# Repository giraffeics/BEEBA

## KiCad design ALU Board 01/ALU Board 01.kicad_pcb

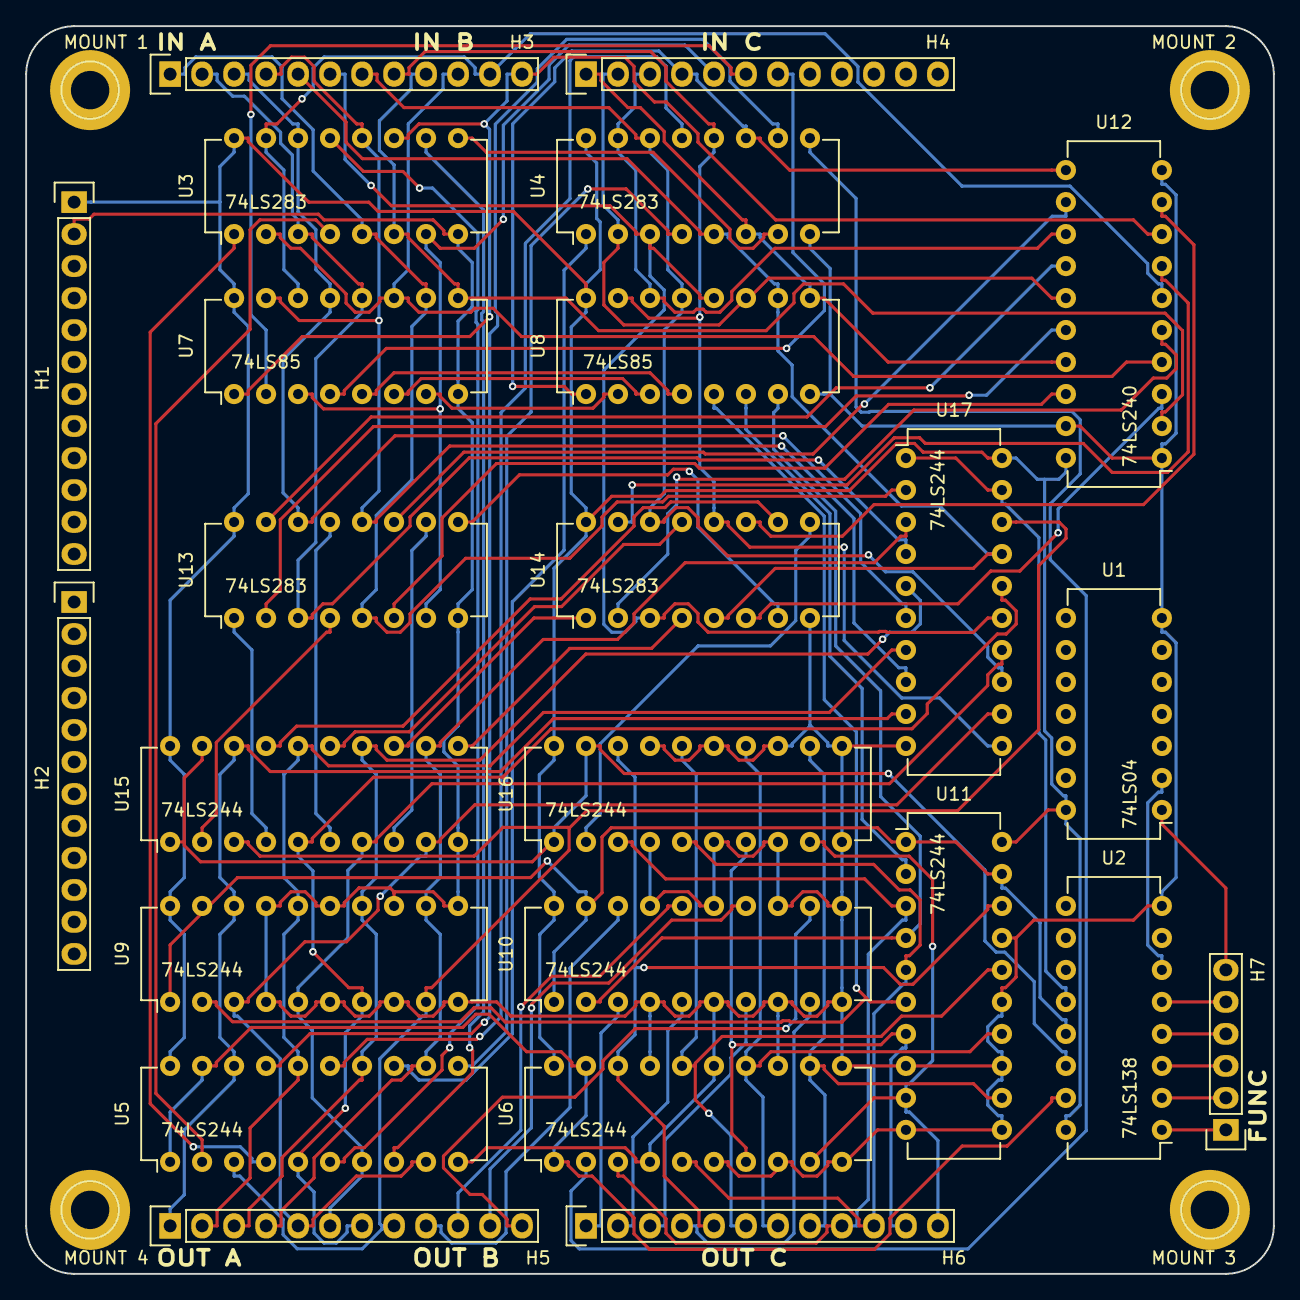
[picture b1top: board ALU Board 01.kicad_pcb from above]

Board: 2 copper layers, 99.1 x 99.1 mm, 28 parts (0 on the bottom side), 90 nets.

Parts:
H1, H2, H3, H4, H5, H6: CONN_01X12; Socket_Strip_Straight_1x12
H7: CONN_01X06; Socket_Strip_Straight_1x06
MOUNT 1, MOUNT 2, MOUNT 3, MOUNT 4: 1pin
U1: 74LS04; DIP-14_W7.62mm
U2: 74LS138; DIP-16_W7.62mm
U3, U4, U13, U14: 74LS283; DIP-16_W7.62mm
U5, U6, U9, U10, U11, U15, U16, U17: 74LS244; DIP-20_W7.62mm
U7, U8: 74LS85; DIP-16_W7.62mm
U12: 74LS240; DIP-20_W7.62mm

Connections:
FS00: U2.15, U5.1, U5.19, U6.1, U6.19
FS01: U2.14, U15.1, U15.19, U16.1, U16.19
FS02: U2.13, U9.1, U9.19, U10.1, U10.19, U11.1, U11.19
FS03: U2.12, U17.1, U17.19
FUNC0: H7.1, U2.1
FUNC1: H7.2, U2.2
FUNC2: H7.3, U2.3
FUNC3: H7.4, U2.4
FUNC4: H7.5, U2.5
FUNC5: H7.6, U1.1
GND: H1.2, U1.7, U2.8, U3.8, U4.8, U5.10, U6.4, U6.6, U6.8, U6.10, U6.11, U6.13, U6.15, U6.17, U7.8, U8.8, U9.4, U9.6, U9.8, U9.10, U9.11, U9.13, U9.15, U9.17, U10.4, U10.6, U10.8, U10.10, U10.11, U10.13, U10.15, U10.17, U11.8, U11.10, U11.11, U11.13, U11.15, U11.17, U12.1, U12.10, U12.19, U13.8, U14.8, U15.10, U16.4, U16.6, U16.8, U16.10, U16.11, U16.13, U16.15, U16.17, U17.10
INA0: H3.1, U3.5, U7.10, U13.5, U17.2
INA1: H3.2, U3.3, U7.12, U13.3, U17.4
INA2: H3.3, U3.14, U7.13, U13.14, U17.6
INA3: H3.4, U3.12, U7.15, U13.12, U17.8
INA4: H3.5, U4.5, U8.10, U14.5, U17.17
INA5: H3.6, U4.3, U8.12, U14.3, U17.15
INA6: H3.7, U4.14, U8.13, U14.14, U17.13
INA7: H3.8, U4.12, U8.15, U14.12, U17.11
INB0: H3.9, U3.6, U7.9, U12.2
INB1: H3.10, U3.2, U7.11, U12.4
INB2: H3.11, U3.15, U7.14, U12.6
INB3: H3.12, U3.11, U7.1, U12.8
INB4: H4.1, U4.6, U8.9, U12.17
INB5: H4.2, U4.2, U8.11, U12.15
INB6: H4.3, U4.15, U8.14, U12.13
INB7: H4.4, U4.11, U8.1, U12.11
INC0: H4.5, U3.7, U7.3, U13.7
INC1: H4.6, U7.2
INC2: H4.7, U7.4
NINB0: U12.18, U13.6
NINB1: U12.16, U13.2
NINB2: U12.14, U13.15
NINB3: U12.12, U13.11
NINB4: U12.3, U14.6
NINB5: U12.5, U14.2
NINB6: U12.7, U14.15
NINB7: U12.9, U14.11
unnamed: U1.2, U2.6
unnamed: U3.1, U5.4
unnamed: U3.4, U5.2
unnamed: U3.9, U4.7
unnamed: U3.10, U5.8
unnamed: U3.13, U5.6
unnamed: U4.1, U5.13
unnamed: U4.4, U5.11
unnamed: U4.9, U6.2
unnamed: U4.10, U5.17
unnamed: U4.13, U5.15
unnamed: U7.5, U8.4
unnamed: U7.6, U8.3
unnamed: U7.7, U8.2
unnamed: U8.7, U10.2, U11.4
unnamed: U8.6, U11.2
unnamed: U8.5, U9.2, U11.6
unnamed: U13.1, U15.4
unnamed: U13.4, U15.2
unnamed: U13.9, U14.7
unnamed: U13.10, U15.8
unnamed: U13.13, U15.6
unnamed: U14.1, U15.13
unnamed: U14.4, U15.11
unnamed: U14.9, U16.2
unnamed: U14.10, U15.17
unnamed: U14.13, U15.15
OUTA0: H5.1, U5.18, U9.18, U15.18, U17.9
OUTA1: H5.2, U5.16, U9.16, U15.16, U17.7
OUTA2: H5.3, U5.14, U9.14, U15.14, U17.5
OUTA3: H5.4, U5.12, U9.12, U15.12, U17.3
OUTA4: H5.5, U5.9, U9.3, U15.9, U17.12
OUTA5: H5.6, U5.7, U9.5, U15.7, U17.14
OUTA6: H5.7, U5.5, U9.7, U15.5, U17.16
OUTA7: H5.8, U5.3, U9.9, U15.3, U17.18
OUTB0: H5.9, U10.18
OUTB1: H5.10, U10.16
OUTB2: H5.11, U10.14
OUTB3: H5.12, U10.12
OUTB4: H6.1, U10.3
OUTB5: H6.2, U10.5
OUTB6: H6.3, U10.7
OUTB7: H6.4, U10.9
OUTC0: H6.5, U6.18, U11.18, U16.18
OUTC1: H6.6, U6.16, U11.16, U16.16
OUTC2: H6.7, U6.14, U11.14, U16.14
OUTC3: H6.8, U6.12, U11.12, U16.12
OUTC4: H6.9, U6.3, U11.3, U16.3
OUTC5: H6.10, U6.5, U11.5, U16.5
OUTC6: H6.11, U6.7, U11.7, U16.7
OUTC7: H6.12, U6.9, U11.9, U16.9
VCC: H1.1, U1.14, U2.16, U3.16, U4.16, U5.20, U6.20, U7.16, U8.16, U9.20, U10.20, U11.20, U12.20, U13.16, U14.16, U15.20, U16.20, U17.20

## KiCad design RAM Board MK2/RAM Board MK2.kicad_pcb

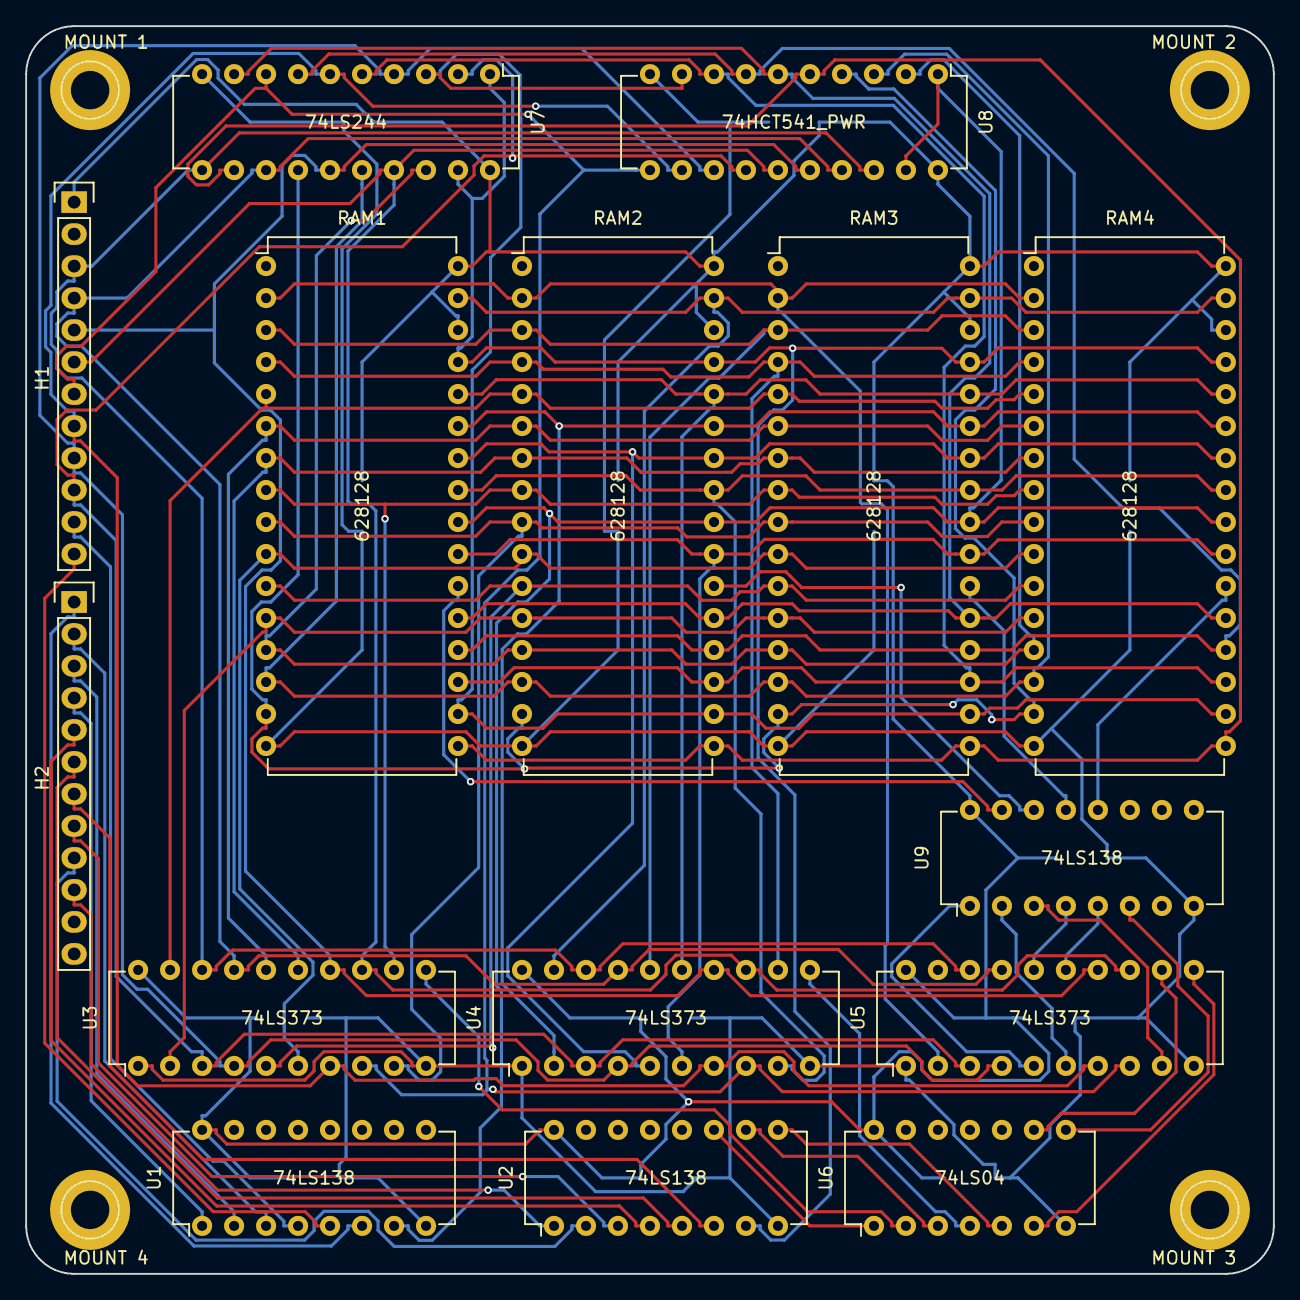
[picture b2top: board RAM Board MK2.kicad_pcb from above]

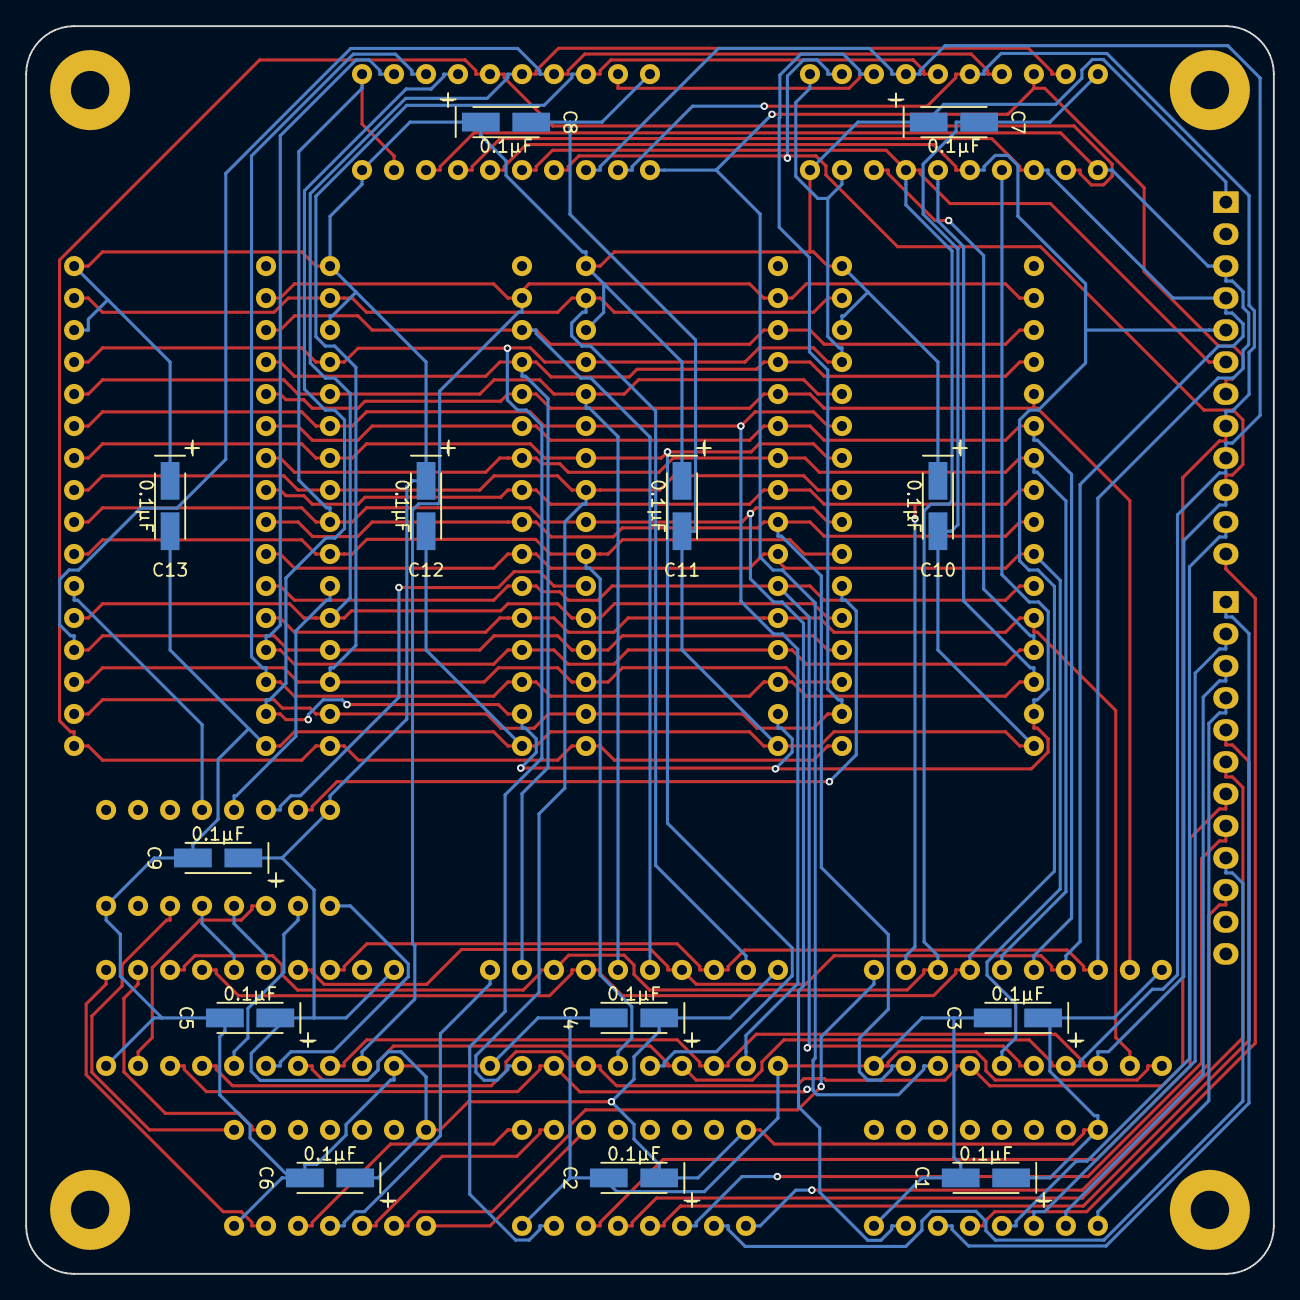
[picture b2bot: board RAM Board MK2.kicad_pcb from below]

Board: 2 copper layers, 99.1 x 99.1 mm, 32 parts (13 on the bottom side), 66 nets.

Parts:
C1, C2, C3, C4, C5, C6, C7, C8, C9, C10, C11, C12, C13: 0.1μF; TantalC_SizeA_EIA-3216_HandSoldering
H1, H2: CONN_01X12; Socket_Strip_Straight_1x12
MOUNT 1, MOUNT 2, MOUNT 3, MOUNT 4: 1pin
RAM1, RAM2, RAM3, RAM4: 628128; DIP-32_W15.24mm
U1, U2, U9: 74LS138; DIP-16_W7.62mm
U3, U4, U5: 74LS373; DIP-20_W7.62mm
U6: 74LS04; DIP-14_W7.62mm
U7: 74LS244; DIP-20_W7.62mm
U8: 74HCT541_PWR; DIP-20_W7.62mm

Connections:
ADD00: RAM1.12, RAM2.12, RAM3.12, RAM4.12, U3.2
ADD01: RAM1.11, RAM2.11, RAM3.11, RAM4.11, U3.5
ADD02: RAM1.10, RAM2.10, RAM3.10, RAM4.10, U3.6
ADD03: RAM1.9, RAM2.9, RAM3.9, RAM4.9, U3.9
ADD04: RAM1.8, RAM2.8, RAM3.8, RAM4.8, U3.12
ADD05: RAM1.7, RAM2.7, RAM3.7, RAM4.7, U3.15
ADD06: RAM1.6, RAM2.6, RAM3.6, RAM4.6, U3.16
ADD07: RAM1.5, RAM2.5, RAM3.5, RAM4.5, U3.19
ADD08: RAM1.27, RAM2.27, RAM3.27, RAM4.27, U4.2
ADD09: RAM1.26, RAM2.26, RAM3.26, RAM4.26, U4.5
ADD10: RAM1.23, RAM2.23, RAM3.23, RAM4.23, U4.6
ADD11: RAM1.25, RAM2.25, RAM3.25, RAM4.25, U4.9
ADD12: RAM1.4, RAM2.4, RAM3.4, RAM4.4, U4.12
ADD13: RAM1.28, RAM2.28, RAM3.28, RAM4.28, U4.15
ADD14: RAM1.3, RAM2.3, RAM3.3, RAM4.3, U4.16
ADD15: RAM1.31, RAM2.31, RAM3.31, RAM4.31, U4.19
ADD16: RAM1.2, RAM2.2, RAM3.2, RAM4.2, U5.2
ADD17: U5.5, U9.1
ADD18: U5.6, U9.2
ADD19: U5.9, U9.3
ADD20: U5.12, U6.9
ADD21: U5.15, U9.5
ADD22: U5.16, U9.4
DATA0: H1.10, U3.3, U4.3, U5.3, U7.2, U8.14
DATA1: H1.9, U3.4, U4.4, U5.4, U7.4, U8.13
DATA2: H1.8, U3.7, U4.7, U5.7, U7.6, U8.12
DATA3: H1.7, U3.8, U4.8, U5.8, U7.8, U8.11
DATA4: H1.6, U3.13, U4.13, U5.13, U7.17, U8.15
DATA5: H1.5, U3.14, U4.14, U5.14, U7.15, U8.16
DATA6: H1.4, U3.17, U4.17, U5.17, U7.13, U8.17
DATA7: H1.3, U3.18, U4.18, U5.18, U7.11, U8.18
GND: C1.2, C2.2, C3.2, C4.2, C5.2, C6.2, C7.2, C8.2, C9.2, C10.2, C11.2, C12.2, C13.2, RAM1.16, RAM2.16, RAM3.16, RAM4.16, U1.8, U2.8, U3.1, U3.10, U4.1, U4.10, U5.1, U5.10, U6.7, U7.10, U8.10, U9.8
unnamed: U3.11, U6.2
unnamed: U4.11, U6.4
unnamed: U5.11, U6.6
unnamed: U6.8, U9.6
RAMS1: RAM1.22, U9.15
RAMS2: RAM2.22, U9.14
RAMS3: RAM3.22, U9.13
RAMS4: RAM4.22, U9.12
READ0: H2.4, U1.1
READ1: H2.3, U1.2
READ2: H2.2, U1.3
READ3: H2.1, U1.6
READ4: H1.12, U1.5
READ5: H1.11, U1.4
RS15: RAM1.24, RAM2.24, RAM3.24, RAM4.24, U1.7, U8.1, U8.19
TD0: RAM1.13, RAM2.13, RAM3.13, RAM4.13, U7.18, U8.2
TD1: RAM1.14, RAM2.14, RAM3.14, RAM4.14, U7.16, U8.3
TD2: RAM1.15, RAM2.15, RAM3.15, RAM4.15, U7.14, U8.4
TD3: RAM1.17, RAM2.17, RAM3.17, RAM4.17, U7.12, U8.5
TD4: RAM1.18, RAM2.18, RAM3.18, RAM4.18, U7.3, U8.9
TD5: RAM1.19, RAM2.19, RAM3.19, RAM4.19, U7.5, U8.8
TD6: RAM1.20, RAM2.20, RAM3.20, RAM4.20, U7.7, U8.7
TD7: RAM1.21, RAM2.21, RAM3.21, RAM4.21, U7.9, U8.6
VCC: C1.1, C2.1, C3.1, C4.1, C5.1, C6.1, C7.1, C8.1, C9.1, C10.1, C11.1, C12.1, C13.1, H1.1, RAM1.30, RAM1.32, RAM2.30, RAM2.32, RAM3.30, RAM3.32, RAM4.30, RAM4.32, U1.16, U2.16, U3.20, U4.20, U5.20, U6.14, U7.20, U8.20, U9.16
WRITE0: H2.10, U2.1
WRITE1: H2.9, U2.2
WRITE2: H2.8, U2.3
WRITE3: H2.7, U2.6
WRITE4: H2.6, U2.5
WRITE5: H2.5, U2.4
WS12: U2.11, U6.1
WS13: U2.10, U6.3
WS14: U2.9, U6.5
WS15: RAM1.29, RAM2.29, RAM3.29, RAM4.29, U2.7, U7.1, U7.19
